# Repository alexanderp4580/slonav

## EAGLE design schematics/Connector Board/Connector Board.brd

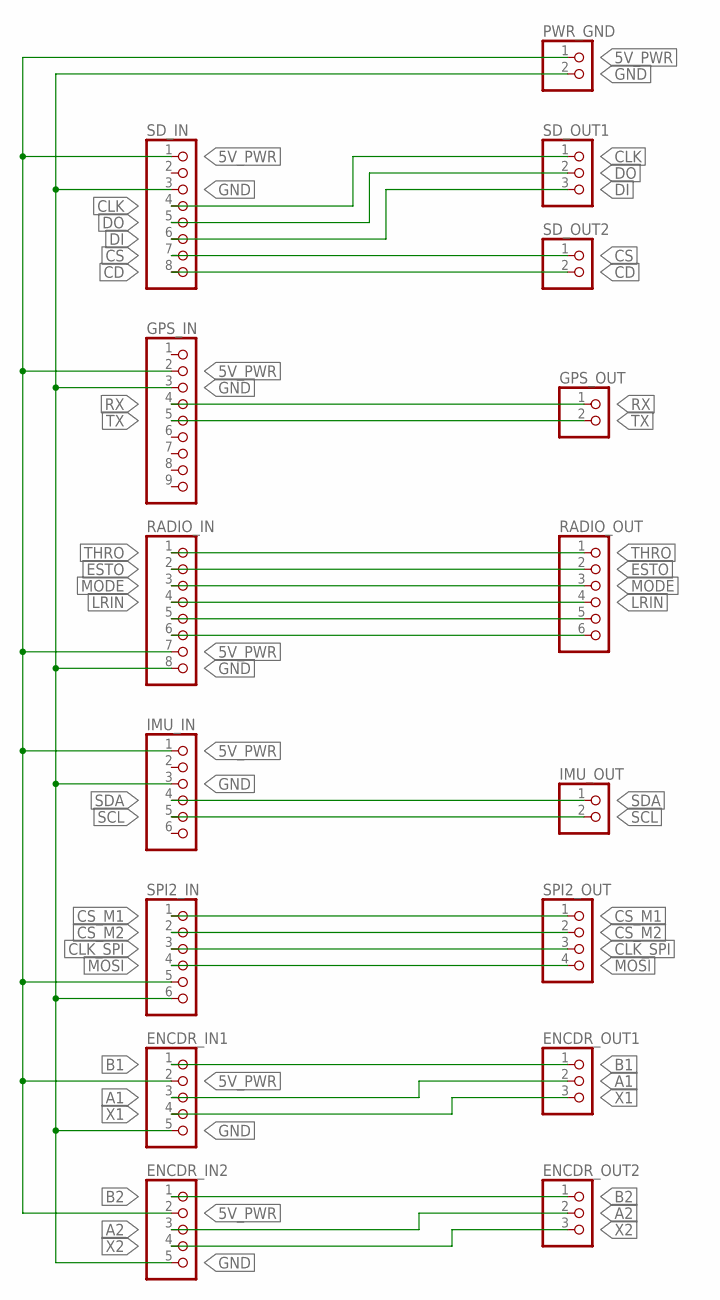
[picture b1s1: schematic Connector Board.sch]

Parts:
ENCDR_IN1, ENCDR_IN2: PINHD-1X5; 1X05
ENCDR_OUT1, ENCDR_OUT2: PINHD-1X3; 1X03
GPS_IN: PINHD-1X9; 1X09
GPS_OUT: PINHD-1X2; 1X02
IMU_IN: PINHD-1X6; 1X06
IMU_OUT: PINHD-1X2; 1X02
PWR_GND: PINHD-1X2; 1X02
RADIO_IN: PINHD-1X8; 1X08
RADIO_OUT: PINHD-1X6; 1X06
SD_IN: PINHD-1X8; 1X08
SD_OUT1: PINHD-1X3; 1X03
SD_OUT2: PINHD-1X2; 1X02
SPI2_IN: PINHD-1X6; 1X06
SPI2_OUT: PINHD-1X4; 1X04

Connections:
5V_PWR: ENCDR_IN1.2, ENCDR_IN2.2, GPS_IN.2, IMU_IN.1, PWR_GND.1, RADIO_IN.7, SD_IN.1, SPI2_IN.5
A1: ENCDR_IN1.3, ENCDR_OUT1.2
A2: ENCDR_IN2.3, ENCDR_OUT2.2
B1: ENCDR_IN1.1, ENCDR_OUT1.1
B2: ENCDR_IN2.1, ENCDR_OUT2.1
CD: SD_IN.8, SD_OUT2.2
CLK: SD_IN.4, SD_OUT1.1
CLK_SPI: SPI2_IN.3, SPI2_OUT.3
CS: SD_IN.7, SD_OUT2.1
CS_M1: SPI2_IN.1, SPI2_OUT.1
CS_M2: SPI2_IN.2, SPI2_OUT.2
DI: SD_IN.6, SD_OUT1.3
DO: SD_IN.5, SD_OUT1.2
ESTO: RADIO_IN.2, RADIO_OUT.2
GND: ENCDR_IN1.5, ENCDR_IN2.5, GPS_IN.3, IMU_IN.3, PWR_GND.2, RADIO_IN.8, SD_IN.3, SPI2_IN.6
LRIN: RADIO_IN.4, RADIO_OUT.4
MODE: RADIO_IN.3, RADIO_OUT.3
MOSI: SPI2_IN.4, SPI2_OUT.4
unnamed: RADIO_IN.5, RADIO_OUT.5
unnamed: RADIO_IN.6, RADIO_OUT.6
RX: GPS_IN.4, GPS_OUT.1
SCL: IMU_IN.5, IMU_OUT.2
SDA: IMU_IN.4, IMU_OUT.1
THRO: RADIO_IN.1, RADIO_OUT.1
TX: GPS_IN.5, GPS_OUT.2
X1: ENCDR_IN1.4, ENCDR_OUT1.3
X2: ENCDR_IN2.4, ENCDR_OUT2.3

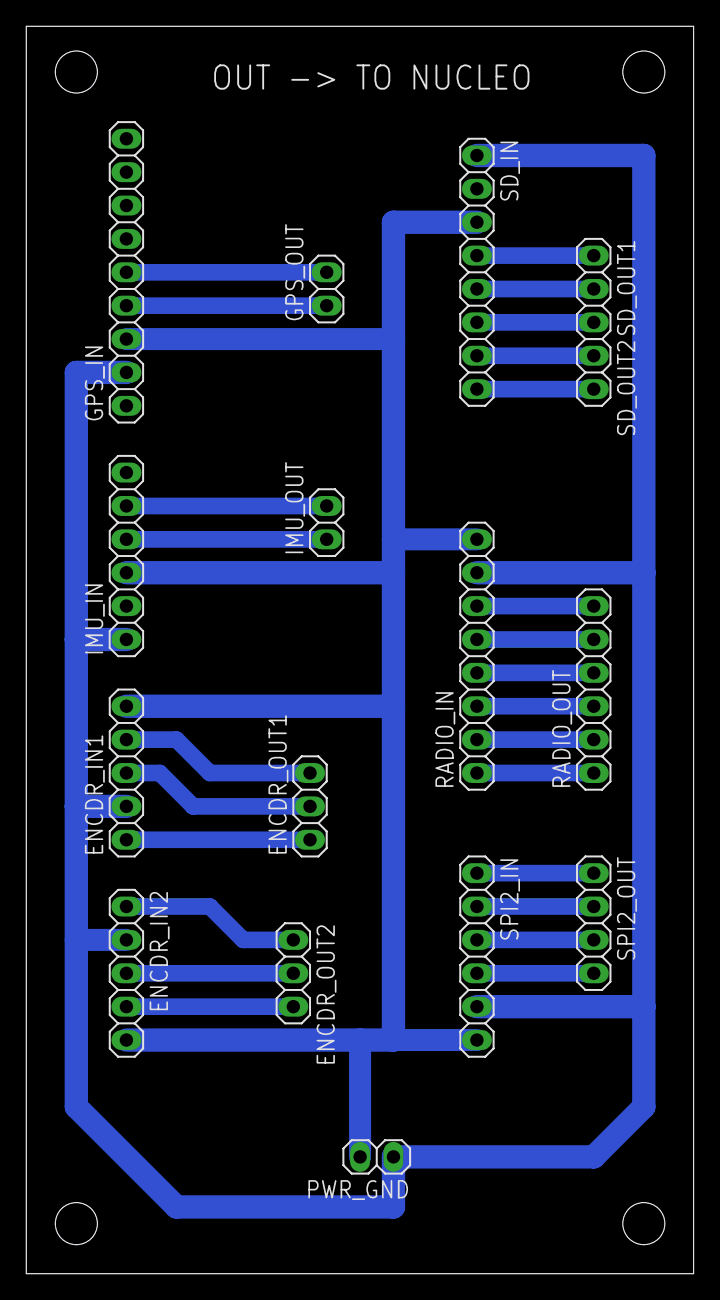
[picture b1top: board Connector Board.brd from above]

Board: 2 copper layers, 50.8 x 94.9 mm, 16 parts (0 on the bottom side), 27 nets.

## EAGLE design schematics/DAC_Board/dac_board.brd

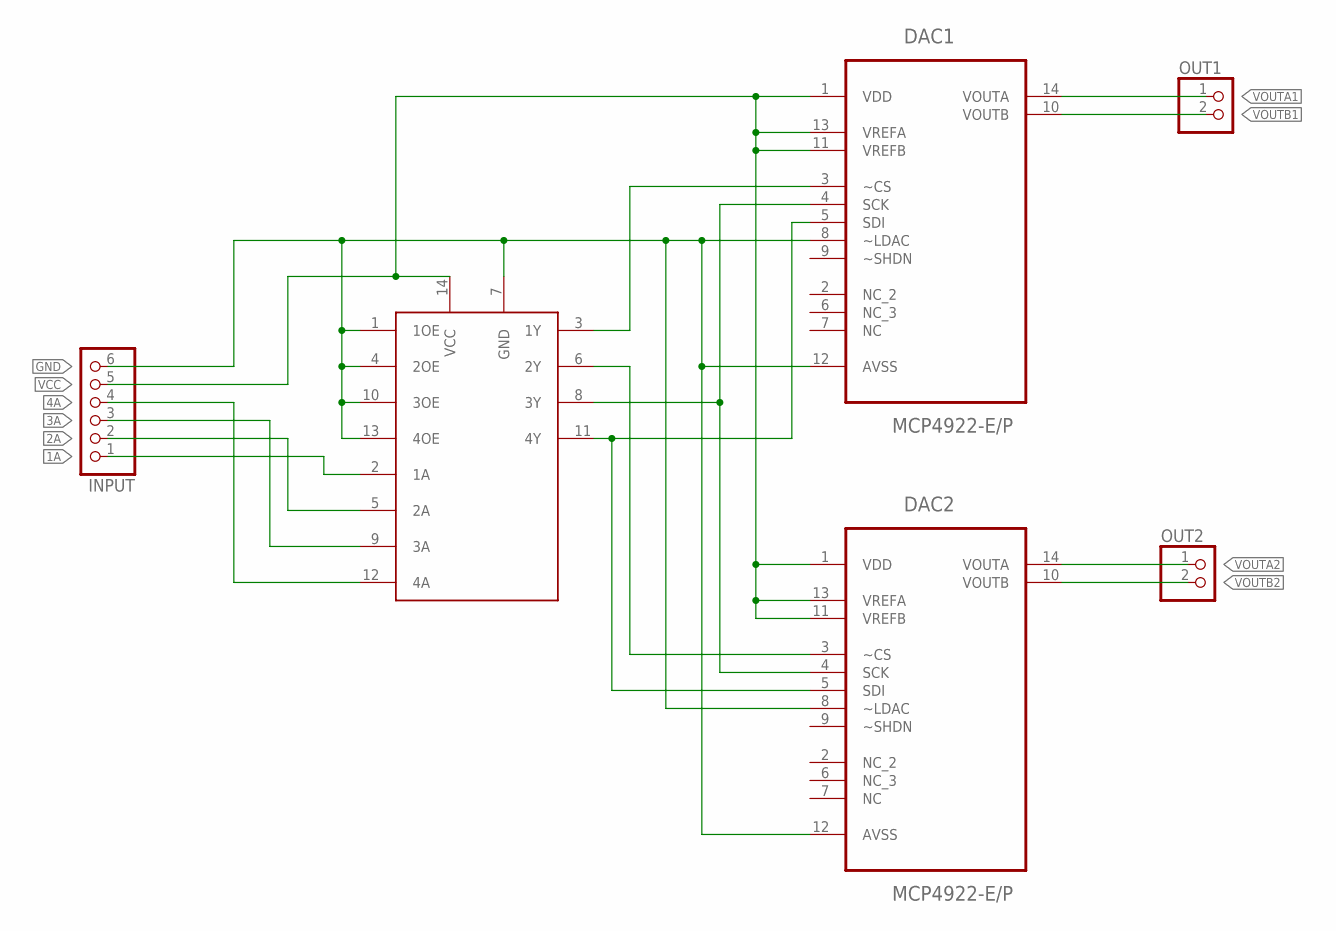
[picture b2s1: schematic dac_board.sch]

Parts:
DAC1, DAC2: MCP4922-E/P; DIP254P762X533-14
INPUT: PINHD-1X6; 1X06
LLS: SN74AHCT125; DIP762W46P254L1930H508Q14
OUT1, OUT2: PINHD-1X2; 1X02

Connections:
1A: INPUT.1, LLS.2 (1A)
1Y: DAC1.3 (~CS), LLS.3 (1Y)
2A: INPUT.2, LLS.5 (2A)
2Y: DAC2.3 (~CS), LLS.6 (2Y)
3A: INPUT.3, LLS.9 (3A)
3Y: DAC1.4 (SCK), DAC2.4 (SCK), LLS.8 (3Y)
4A: INPUT.4, LLS.12 (4A)
4Y: DAC1.5 (SDI), DAC2.5 (SDI), LLS.11 (4Y)
GND: DAC1.8 (~LDAC), DAC1.12 (AVSS), DAC2.8 (~LDAC), DAC2.12 (AVSS), INPUT.6, LLS.1 (1OE), LLS.4 (2OE), LLS.7 (GND), LLS.10 (3OE), LLS.13 (4OE)
VCC: DAC1.1 (VDD), DAC1.11 (VREFB), DAC1.13 (VREFA), DAC2.1 (VDD), DAC2.11 (VREFB), DAC2.13 (VREFA), INPUT.5, LLS.14 (VCC)
VOUTA1: DAC1.14 (VOUTA), OUT1.1
VOUTA2: DAC2.14 (VOUTA), OUT2.1
VOUTB1: DAC1.10 (VOUTB), OUT1.2
VOUTB2: DAC2.10 (VOUTB), OUT2.2

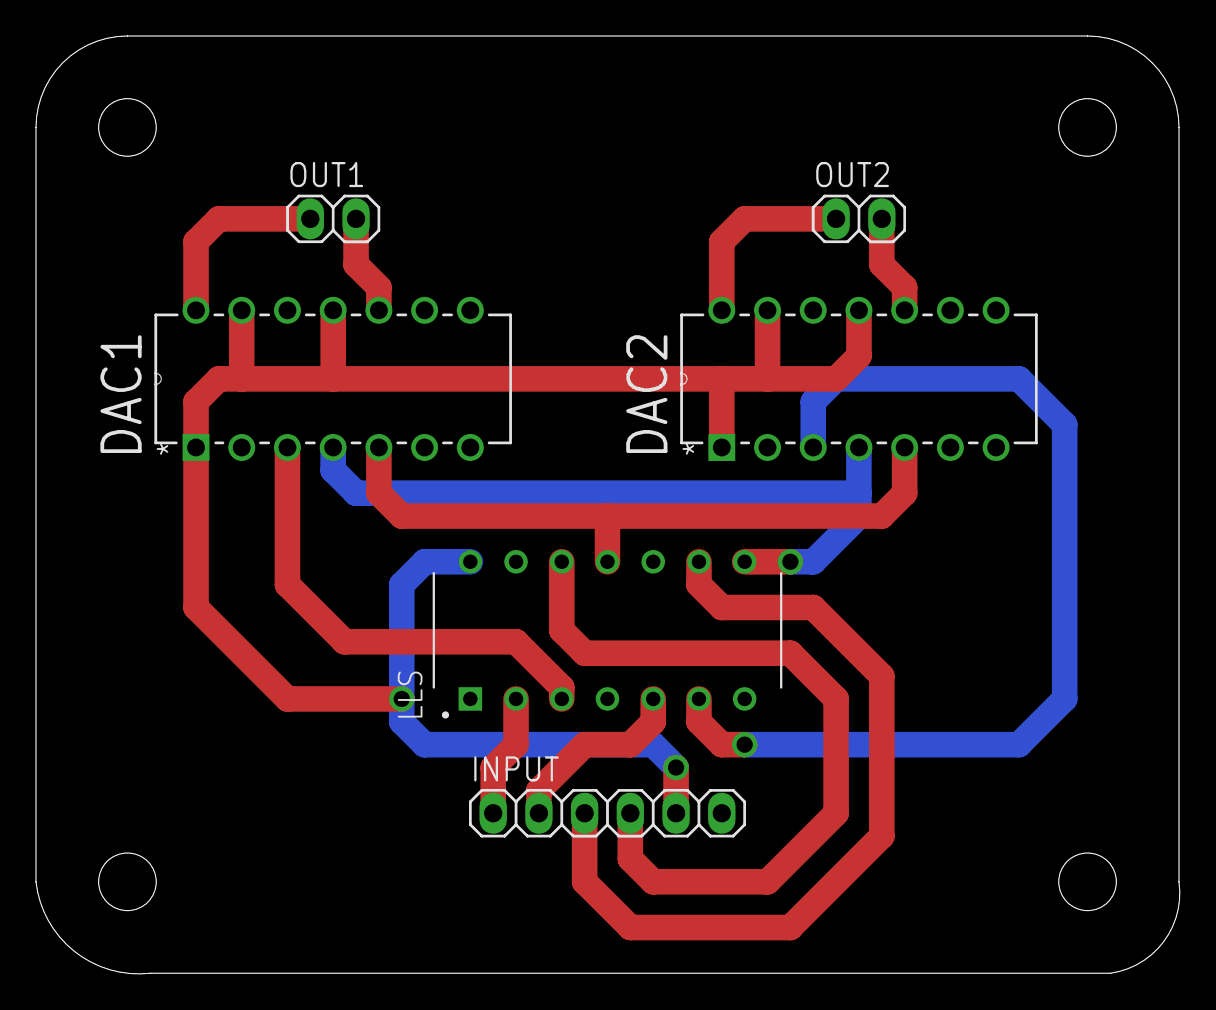
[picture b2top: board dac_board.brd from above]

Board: 2 copper layers, 63.5 x 52.1 mm, 6 parts (0 on the bottom side), 14 nets.

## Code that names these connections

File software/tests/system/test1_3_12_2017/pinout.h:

/**
 *Pinouts for the SLONav test vehical prototype
 *TU 3/07/2017
 *
**/



/* Nucleo Motor Cape */
const PinName IN1A = PB_4;
const PinName IN2A = PB_5;
const PinName IN1B = PA_1;
const PinName IN2B = PA_0;
const PinName ENA  = PA_10;
const PinName ENB  = PC_1;

/* Encoders */
const PinName CHA1 = PA_8;
const PinName CHB1 = PB_10;
const PinName CHA2 = PA_7;
const PinName CHB2 = PB_6;

/* IMU */
const PinName IMDA = I2C_SDA;
const PinName IMCL = I2C_SCL;

/* GPS */
const PinName GPTX = PA_0;
const PinName GPRX = PA_1;

/* radio */
const PinName THRO = PA_5;
const PinName LRIN = PB_0;
const PinName MODE = PB_3;
const PinName ESTO = PA_9;

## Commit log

2017-01-19 Initial commit of Simulink vehicle model
2017-01-19 Created Matlab script to run Simulink model
2017-01-30 Moved stuff to folder and stuff
2017-01-30 Created electrical echematic file (incomplete)
2017-01-30 Stupid changes
2017-01-30 Added eagle stuff to git ignore
2017-01-30 Added test program for sensor integration. Currently just IMU
2017-01-30 Added placeholder for braking and vehicle model
2017-01-30 Finished Schematic Overview Drawing for CDR
2017-02-03 Added some more of the vehicle dynamics
2017-02-03 Added rest of vehicle model and modified motor models
2017-02-03 Changed name of test_vehicle script
2017-02-04 Worked on vehicle simulation, stuff is messed up yo
2017-02-05 Went with skid steering model with no modification. Started steering control loop
2017-02-05 Steering control is WIP
2017-02-06 Added Motor controller and analog input for brake
2017-02-06 Updated model, it sucks... I gave up
2017-02-07 Fixed steering model, WOoOoOoOoOo
2017-02-07 Stuffy stuff
2017-02-08 Final version of steering model for CDR
2017-02-08 Added some stuff for velocity control
2017-02-23 Removed old code, added directory for schematics
2017-02-23 Added folder structor for final design
2017-02-23 blah
2017-02-27 Added mbed library and make file
2017-02-27 Modified folder structure
2017-02-27 Mo modifications, yo
2017-02-27 Added imu driver files from old project
2017-02-28 Worked on IMU driver, currently not working
2017-02-28 Still a work in progress
2017-03-03 Fixed drivers and test file. Still needs comments
2017-03-05 Added files for motor testing on scale model
2017-03-05 Removed unecessary folder
2017-03-06 Got motor driver working, encoder and pid need to be written
2017-03-07 added gps
2017-03-07 added test file for integrateing motors and sensors
2017-03-07 Added PID and encoder libraries. Wrote basic test for encoders.
2017-03-07 working through building the test but I think i broke it
2017-03-07 added sanity check
2017-03-08 Added system test file. Works except for we have a pin conflict
2017-03-09 Added file for new test and updated the pinout to solve GPS conflict
2017-03-12 Changed some stuff, added files for sensor fusion to test
2017-03-12 Removed some unnecessary files and began implementing TinyEKF
2017-03-13 added radio control directory
2017-03-13 added shitty test
2017-03-14 added some stuff
2017-03-16 Started adding some stuff for PID control of motors
2017-04-05 Added folder for SDCard library and modified make file to use new mbed directory
2017-04-06 Worked on SD Card stuffff
2017-04-09 Got SD card working with platform. Test code write some readings from IMU.
2017-04-09 Removed TinyEKF due to git issue
2017-04-12 added test file for sd card and all sensors and the motors
2017-04-13 Fixed data test file.
2017-04-13 Changed the data collection program to show some behavior of final design
2017-04-13 Added data file from first good STU test
2017-04-15 added radio control to the data collection program
2017-04-15 cleaned up the data collection program, output should be csv (untested)
2017-04-16 Removed build files from tests and added .d files to .gitignore
2017-04-16 Changed makefiles to utilize single mbed library (removing redundant copies)
2017-04-17 Added files and began working on sensor fusion code
2017-04-17 Added folders for steering control and acceleration control testing
2017-04-20 Rmoved old test folders and reorganized makefiles
2017-04-22 Filled in the Map Parser. Car can now load a full map and will do some small checking for safety
2017-04-22 removed a swp file
2017-04-24 Steering test ready for evaluation
2017-04-29 somthing branchy happened, moved mapp functions to seperate files
2017-04-29 started working on skeleton archetecture for final program
2017-04-29 Stuffy mcstuff
2017-04-30 Started implementing EKF sensor fusion
2017-04-30 broken skeleton I need real food that sandwhich was empty
2017-04-30 gps again
2017-05-01 Worked on some stuff stuff
2017-05-03 finished skeleton still not in a compilable state
2017-05-04 Updates to skeleton code, still not compiling yet
2017-05-14 Changed PID controller class
2017-05-14 Updated pinout and wrote test for kelly motor controller hardware
2017-05-14 Tested some debugging using openOCD and GDB
2017-05-15 Wrote test for DAC chips
2017-05-19 Tested DAC board
2017-05-19 Started modifying acceleration control loop
2017-05-20 Control stuffs
2017-05-22 FATE additions
2017-05-22 Added some pins for final brake driver
2017-05-22 Wrote class for controlling linear actuator
2017-05-22 Added code for braking actuator
2017-05-26 added skull and more radio inputs
2017-05-26 Began integrating test files into skeleton
2017-05-26 Worked on "Skeleton" code for radio control
2017-05-26 Changed encoder reading function. Added full brake when emergency brake is actuated.
2017-05-27 Failed track day code
2017-05-29 Got full scale radio control partly functional (skeleton). Created new pinout header for model.
2017-05-29 Got steering control working
2017-05-29 Implemented different driver for GPS. Added data logging to steering control test.
2017-05-30 Wrote acceleration control (doesn't work well at all)
2017-06-05 Added useful documentation
